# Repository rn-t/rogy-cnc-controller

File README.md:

# Rogy-CNC-Controller

## PCB

## Firmware

### キーマップの書き換え

キーマップを書き換えるには`firmware/Core/Inc/settings.h`の該当する`keycodes`と`modifiers`の要素を書き換えます．

注) `keycode`は`ASCII`などではありません．[ここ](http://www2d.biglobe.ne.jp/~msyk/keyboard/layout/usbkeycode.html)などを参照して`keycode`を調べてください．

### LED

LEDの色を変更するには`firmware/Core/Inc/settings.h`の該当する`LEDsettings`の値を変更します。値はRGBの順で並んでいます。

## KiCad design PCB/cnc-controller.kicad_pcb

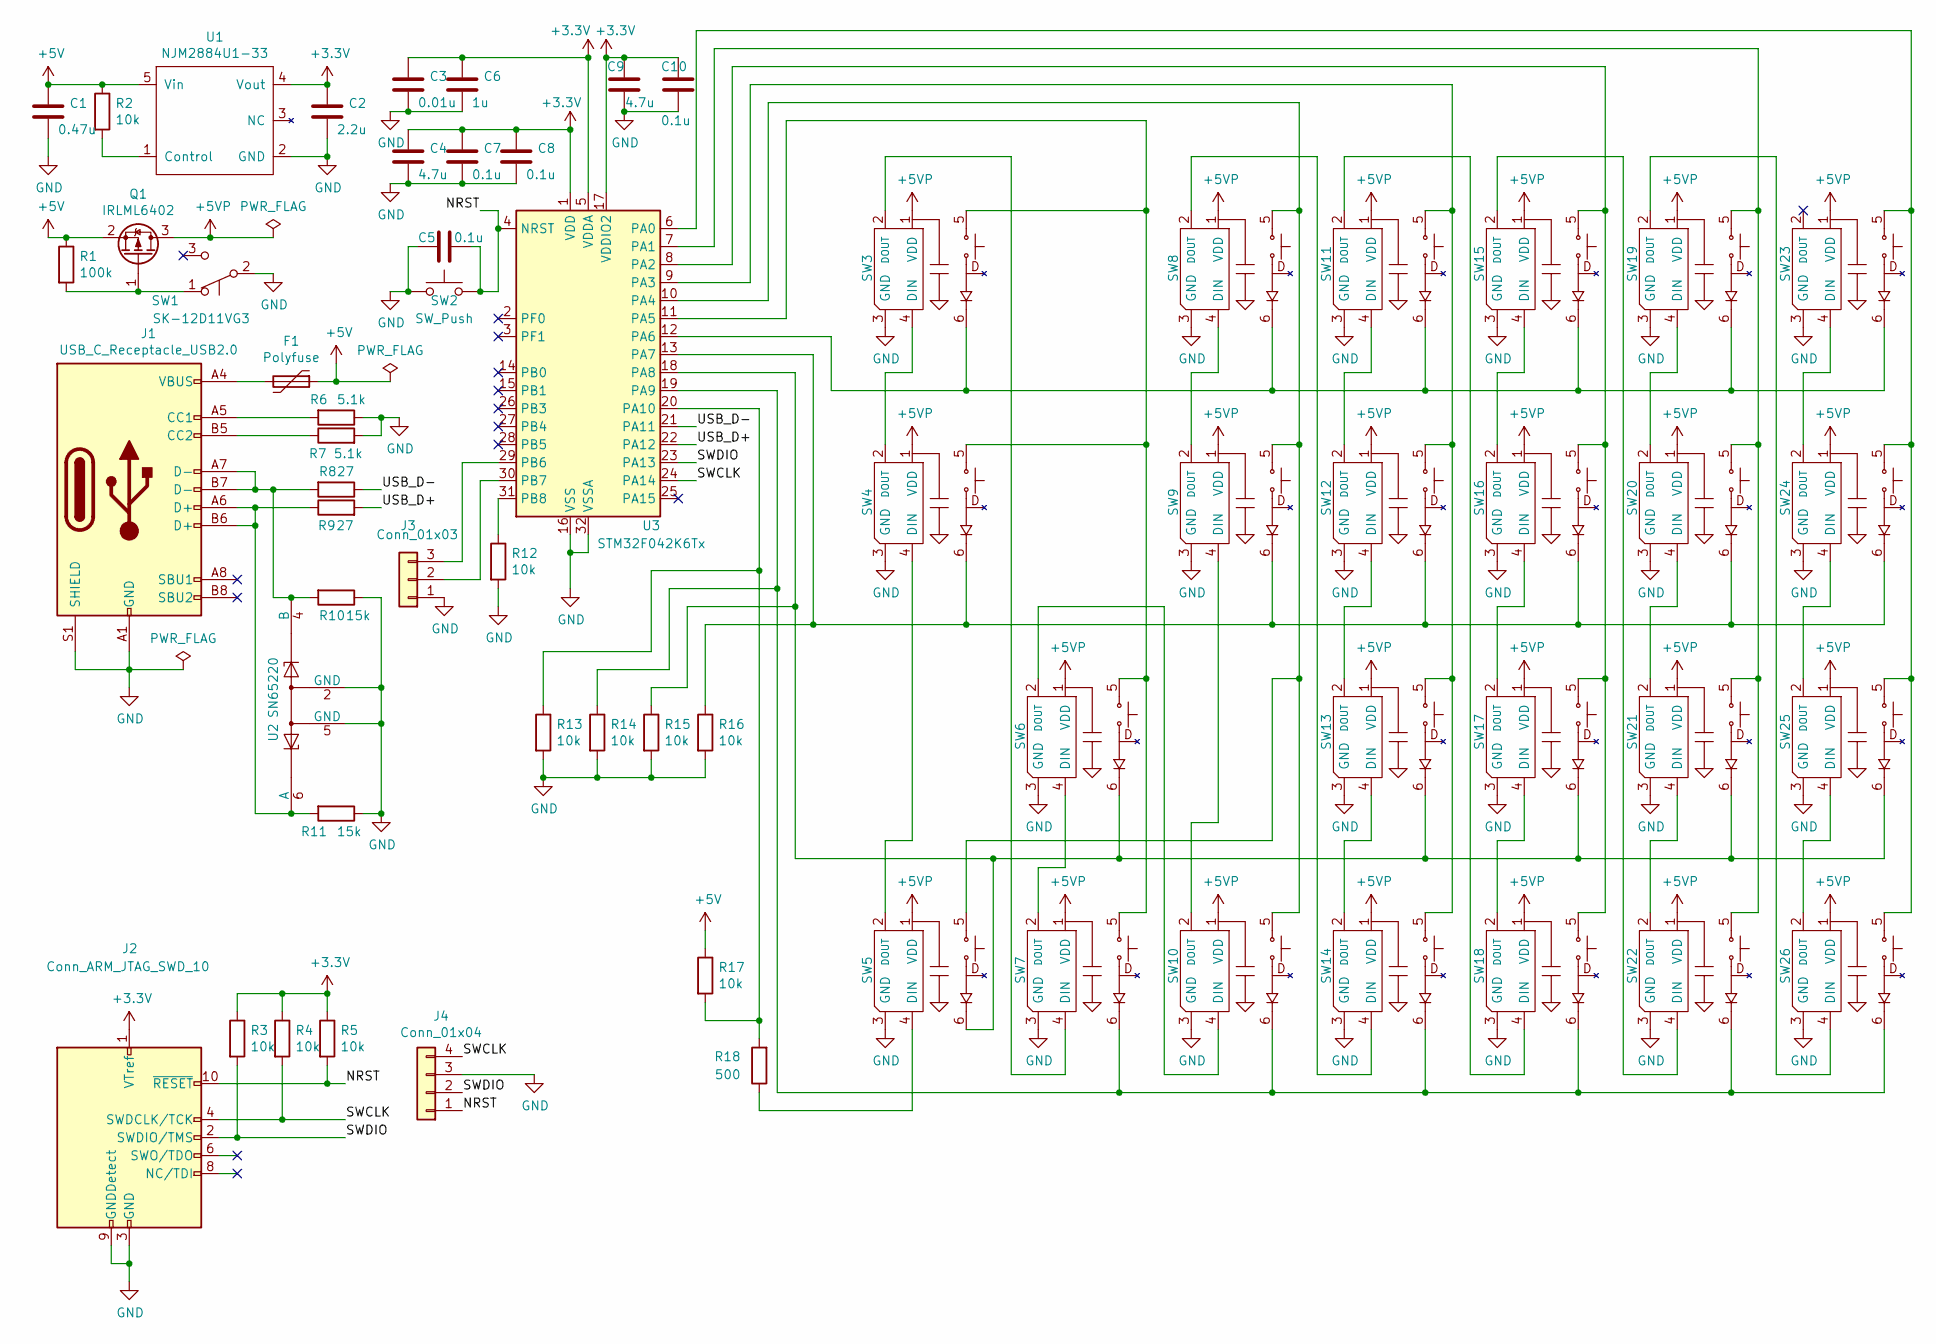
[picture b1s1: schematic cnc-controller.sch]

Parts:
C1: 0.47u; C_0402_1005Metric_Pad0.74x0.62mm_HandSolder
C2: 2.2u; C_0805_2012Metric_Pad1.18x1.45mm_HandSolder
C3: 0.01u; C_0603_1608Metric_Pad1.08x0.95mm_HandSolder
C4, C9: 4.7u; C_0603_1608Metric_Pad1.08x0.95mm_HandSolder
C5, C7, C8, C10: 0.1u; C_0603_1608Metric_Pad1.08x0.95mm_HandSolder
C6: 1u; C_0603_1608Metric_Pad1.08x0.95mm_HandSolder
F1: Polyfuse; Fuse_0603_1608Metric_Pad1.05x0.95mm_HandSolder
J1: USB_C_Receptacle_USB2.0; USBC_5077CR-16-SMC2-BK-TR
J2: Conn_ARM_JTAG_SWD_10; PinHeader_2x05_P1.27mm_Vertical
J3: Conn_01x03; PinHeader_1x03_P2.54mm_Vertical
J4: Conn_01x04; PinHeader_1x04_P2.54mm_Vertical
Q1: IRLML6402; SOT-23
R1: 100k; R_0603_1608Metric_Pad0.98x0.95mm_HandSolder
R2, R3, R4, R5, R12, R13, R14, R15, R16, R17: 10k; R_0603_1608Metric_Pad0.98x0.95mm_HandSolder
R6, R7: 5.1k; R_0603_1608Metric_Pad0.98x0.95mm_HandSolder
R8, R9: 27; R_0603_1608Metric_Pad0.98x0.95mm_HandSolder
R10, R11: 15k; R_0603_1608Metric_Pad0.98x0.95mm_HandSolder
R18: 500; R_0603_1608Metric_Pad0.98x0.95mm_HandSolder
SW1: SK-12D11VG3; SW_SK-12D11VG3
SW2: SW_Push; SW_TVBP06-B043CB-B
SW3, SW4, SW5, SW6, SW7, SW8, SW9, SW10, SW11, SW12, SW13, SW14, SW15, SW16, SW17, SW18, SW19, SW20, SW21, SW22, SW23, SW24, SW25, SW26: sw_unit; kailh_chocv1_unit
U1: NJM2884U1-33; SOT-89-5_Handsoldering
U2: SN65220; SOT-23-6
U3: STM32F042K6Tx; LQFP-32_7x7mm_P0.8mm

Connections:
+3V3: C2.1, C3.1, C4.1, C6.1, C7.1, C8.1, C9.1, C10.1, J2.1 (VTref), R3.1, R4.1, R5.1, U1.4 (Vout), U3.1 (VDD), U3.5 (VDDA), U3.17 (VDDIO2); also elsewhere on the board
+5V: C1.1, F1.1, Q1.2 (S), R1.1, R2.1, R17.1, U1.5 (Vin)
+5VP: Q1.3 (D), SW3.1 (VDD), SW4.1 (VDD), SW5.1 (VDD), SW6.1 (VDD), SW7.1 (VDD), SW8.1 (VDD), SW9.1 (VDD), SW10.1 (VDD), SW11.1 (VDD), SW12.1 (VDD), SW13.1 (VDD), SW14.1 (VDD), SW15.1 (VDD), SW16.1 (VDD), SW17.1 (VDD), SW18.1 (VDD), SW19.1 (VDD), SW20.1 (VDD), SW21.1 (VDD), SW22.1 (VDD), SW23.1 (VDD), SW24.1 (VDD), SW25.1 (VDD), SW26.1 (VDD)
/NRST: C5.1, J2.10 (~RESET~), J4.1, R5.2, SW2.2, U3.4 (NRST); also elsewhere on the board
/SWCLK: J2.4 (SWDCLK/TCK), J4.4, R4.2, U3.24 (PA14); also elsewhere on the board
/SWDIO: J2.2 (SWDIO/TMS), J4.2, R3.2, U3.23 (PA13); also elsewhere on the board
/USB_D+: R9.2, U3.22 (PA12)
/USB_D-: R8.1, U3.21 (PA11)
GND: C1.2, C2.2, C3.2, C4.2, C5.2, C6.2, C7.2, C8.2, C9.2, C10.2, J1.A1 (GND), J1.A12 (GND), J1.B1 (GND), J1.B12 (GND), J1.S1 (SHIELD), J2.3 (GND), J2.5 (GND), J2.9 (GNDDetect), J3.1, J4.3, R6.1, R7.2, R10.1, R11.1, R12.2, R13.2, R14.2, R15.2, R16.2, SW1.2 (B), SW2.1, SW3.3 (GND), SW4.3 (GND), SW5.3 (GND), SW6.3 (GND), SW7.3 (GND), SW8.3 (GND), SW9.3 (GND), SW10.3 (GND), SW11.3 (GND), SW12.3 (GND), SW13.3 (GND), SW14.3 (GND), SW15.3 (GND), SW16.3 (GND), SW17.3 (GND), SW18.3 (GND), SW19.3 (GND), SW20.3 (GND), SW21.3 (GND), SW22.3 (GND), SW23.3 (GND), SW24.3 (GND), SW25.3 (GND), SW26.3 (GND), U1.2 (GND), U2.2 (GND), U2.5 (GND), U3.16 (VSS), U3.32 (VSSA); also elsewhere on the board
unnamed: F1.2, J1.A4 (VBUS), J1.A9 (VBUS), J1.B4 (VBUS), J1.B9 (VBUS)
unnamed: J1.A5 (CC1), R6.2
unnamed: J1.A6 (D+), J1.B6 (D+), R9.1, R11.2, U2.6 (A)
unnamed: J1.A7 (D-), J1.B7 (D-), R8.2, R10.2, U2.4 (B)
unnamed: J1.B5 (CC2), R7.1
unnamed 19: J3.2, U3.30 (PB7); also elsewhere on the board
unnamed 20: J3.3, U3.29 (PB6); also elsewhere on the board
unnamed: Q1.1 (G), R1.2, SW1.1 (A)
unnamed: R2.2, U1.1 (Control)
unnamed: R12.1, U3.31 (PB8)
unnamed: R13.1, R17.2, R18.2, U3.20 (PA10)
unnamed: R14.1, SW7.6, SW10.6, SW14.6, SW18.6, SW22.6, SW26.6, U3.19 (PA9)
unnamed: R15.1, SW5.6, SW6.6, SW13.6, SW17.6, SW21.6, SW25.6, U3.18 (PA8)
unnamed: R16.1, SW4.6, SW9.6, SW12.6, SW16.6, SW20.6, SW24.6, U3.13 (PA7)
unnamed: R18.1, SW5.4 (DIN)
unnamed: SW3.2 (DOUT), SW7.4 (DIN)
unnamed: SW3.4 (DIN), SW4.2 (DOUT)
unnamed: SW3.5, SW4.5, SW6.5, SW7.5, U3.11 (PA5)
unnamed: SW4.4 (DIN), SW5.2 (DOUT)
unnamed: SW6.4 (DIN), SW7.2 (DOUT)
unnamed: SW8.4 (DIN), SW9.2 (DOUT)
unnamed: SW9.4 (DIN), SW10.2 (DOUT)
unnamed: SW6.2 (DOUT), SW10.4 (DIN)
unnamed: SW5.5, SW8.5, SW9.5, SW10.5, U3.10 (PA4)
unnamed: SW11.2 (DOUT), SW18.4 (DIN)
unnamed: SW11.4 (DIN), SW12.2 (DOUT)
unnamed: SW11.5, SW12.5, SW13.5, SW14.5, U3.9 (PA3)
unnamed: SW3.6, SW8.6, SW11.6, SW15.6, SW19.6, SW23.6, U3.12 (PA6)
unnamed: SW12.4 (DIN), SW13.2 (DOUT)
unnamed: SW13.4 (DIN), SW14.2 (DOUT)
unnamed: SW8.2 (DOUT), SW14.4 (DIN)
unnamed: SW15.2 (DOUT), SW22.4 (DIN)
unnamed: SW15.4 (DIN), SW16.2 (DOUT)
unnamed: SW15.5, SW16.5, SW17.5, SW18.5, U3.8 (PA2)
unnamed: SW16.4 (DIN), SW17.2 (DOUT)
unnamed: SW17.4 (DIN), SW18.2 (DOUT)
unnamed: SW19.2 (DOUT), SW26.4 (DIN)
unnamed: SW19.4 (DIN), SW20.2 (DOUT)
unnamed: SW19.5, SW20.5, SW21.5, SW22.5, U3.7 (PA1)
unnamed: SW20.4 (DIN), SW21.2 (DOUT)
unnamed: SW21.4 (DIN), SW22.2 (DOUT)
unnamed: SW23.4 (DIN), SW24.2 (DOUT)
unnamed: SW23.5, SW24.5, SW25.5, SW26.5, U3.6 (PA0)
unnamed: SW24.4 (DIN), SW25.2 (DOUT)
unnamed: SW25.4 (DIN), SW26.2 (DOUT)

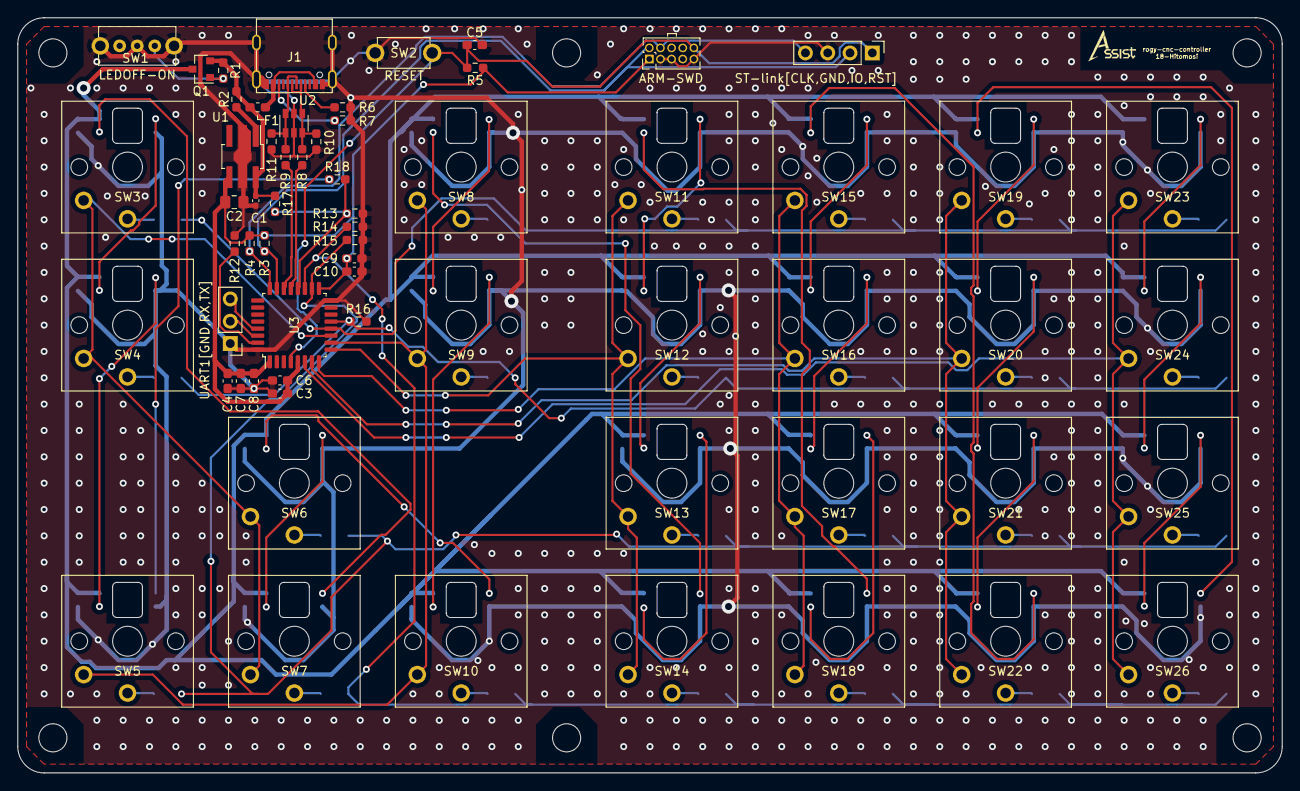
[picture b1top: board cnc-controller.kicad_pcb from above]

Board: 2 copper layers, 144.0 x 86.0 mm, 63 parts (0 on the bottom side), 54 nets.

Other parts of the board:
ARM-SWD: Conn_ARM_JTAG_SWD_10; PinHeader_2x05_P1.27mm_Vertical
ST-link[CLK,GND,IO,RST]: Conn_01x04; PinHeader_1x04_P2.54mm_Vertical
UART1[GND,RX,TX]: Conn_01x03; PinHeader_1x03_P2.54mm_Vertical

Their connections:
+3V3: ARM-SWD.1; also elsewhere on the board
/NRST: ARM-SWD.10, ST-link[CLK,GND,IO,RST].1; also elsewhere on the board
/SWCLK: ARM-SWD.4, ST-link[CLK,GND,IO,RST].4; also elsewhere on the board
/SWDIO: ARM-SWD.2, ST-link[CLK,GND,IO,RST].2; also elsewhere on the board
GND: ARM-SWD.3, ARM-SWD.5, ARM-SWD.9, ST-link[CLK,GND,IO,RST].3, UART1[GND,RX,TX].1; also elsewhere on the board
unnamed 19: UART1[GND,RX,TX].2; also elsewhere on the board
unnamed 20: UART1[GND,RX,TX].3; also elsewhere on the board

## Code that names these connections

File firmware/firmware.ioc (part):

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PA6.GPIOParameters=GPIO_PuPd
Mcu.UserName=STM32F042K6Ux
PA9.GPIOParameters=GPIO_PuPd
PA11.Mode=Device
PA9.GPIO_PuPd=GPIO_PULLDOWN
RCC.SYSCLKSource=RCC_SYSCLKSOURCE_HSI48
PA13.Signal=SYS_SWDIO
PA12.Signal=USB_DP
PA9.Signal=GPIO_Input
PA8.GPIOParameters=GPIO_PuPd
PA10.GPIO_ModeDefaultPP=GPIO_MODE_AF_OD
PA1.Signal=GPIO_Output
PA7.GPIO_PuPd=GPIO_PULLDOWN
PA5.Signal=GPIO_Output
board=custom
PA6.GPIO_PuPd=GPIO_PULLDOWN
PA14.Mode=Serial_Wire
PA10.GPIOParameters=GPIO_ModeDefaultPP
PA8.Signal=GPIO_Input
PA13.Mode=Serial_Wire
Mcu.Name=STM32F042K(4-6)Ux
PA2.Signal=GPIO_Output
PA0.Signal=GPIO_Output
PA4.Signal=GPIO_Output
RCC.SYSCLKFreq_VALUE=48000000
Mcu.Package=UFQFPN32
PA6.Signal=GPIO_Input
PA12.Mode=Device
PA11.Signal=USB_DM
PA10.Signal=S_TIM1_CH3
PA14.Signal=SYS_SWCLK
PA8.GPIO_PuPd=GPIO_PULLDOWN
PA7.GPIOParameters=GPIO_PuPd
PA3.Signal=GPIO_Output
PA7.Signal=GPIO_Input

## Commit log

2021-08-11 キーマトリクスとLEDの回路図を作成
2021-08-13 USBのデータ線の保護素子を変更 USB周りの配線を変更及び書き直し
2021-08-14 3.3Vレギュレータを追加 マイコンの電源用コンデンサを追加 VBUS付近にPWR_FLAGを追加
2021-08-14 USB-Cコネクタのフットプリントを作成し、追加
2021-08-15 キースイッチのフットプリントを作成
2021-08-15 キーマトリクスにプルダウン抵抗を追加 LED電源用スイッチの回路を追加
2021-08-16 リセットスイッチを追加 キーユニットに作図補助線を追加 スイッチ用のフットプリント2つ(トグルスイッチとプッシュスイッチ)用を作成
2021-08-16 フットプリントの関連付けを行った
2021-08-17 回路図上USBコネクタを2.0用のものに変更
2021-08-17 基板の作成を開始 あらかた終了したが、外形線との間隔をあける必要あり
2021-08-18 基板の配線が終了。ねじ穴を開けるために一部変更する必要あり。
2021-08-19 基板が完成 ロゴを追加 ガーバーファイルを追加 gitignoreをzipを無視するように変更
2021-09-05 add .gitignore
2021-09-05 add firmware
2021-09-05 fixed comment in keymap.h
2021-09-05 add comments in main.c
2021-09-06 Fixed the place of hUsbDeviceFS declaration in main.c
2021-09-06 renamed .ioc file
2021-09-06 Change GPIO settings PA6-9 NoPullupAndNoPulldown -> Pulldown
2021-09-06 translated comments in main.c JP->EN because of text garbling
2021-09-06 PCBが完成
2021-09-07 fixed bugs
2021-09-07 removed keymatrix.h
2021-09-07 changed comment
2021-09-07 remove "#include "keymatrix"" because it's no longer used.
2021-09-07 add README.md
2021-09-07 add br
2021-09-09 Enable timer interrupt
2021-09-09 fixed comments in main.c
2021-09-09 change PA10 and TIM1 settings PA10->TIM1_CH3, OpenDrain TIM1 CH3 -> PWM generation
2021-09-09 change report rate 1000Hz
2021-09-09 change settings about TIM1_CH3 Counter Period, DMA
2021-09-09 Change compiler optimization level
2021-10-15 change DMA settings HALFWORD->BYTE & NORMAL->CIRCULAR
2021-10-15 add functions about sk6812mini-e
2021-10-15 add codes to light LEDs for test
2021-10-16 Change TIM1 Counter Period 72->60-1
2021-10-26 refactoring
2021-10-26 refuctoring
2021-10-27 回路図のpdfを追加
2021-10-27 回路図を修正
2021-10-27 add explanation about LEDs in README.md
2022-03-06 change polling rate 1000Hz -> 100Hz
